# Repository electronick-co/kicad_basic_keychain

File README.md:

# kicad_basic_keychain
a basic keychain made with kicad

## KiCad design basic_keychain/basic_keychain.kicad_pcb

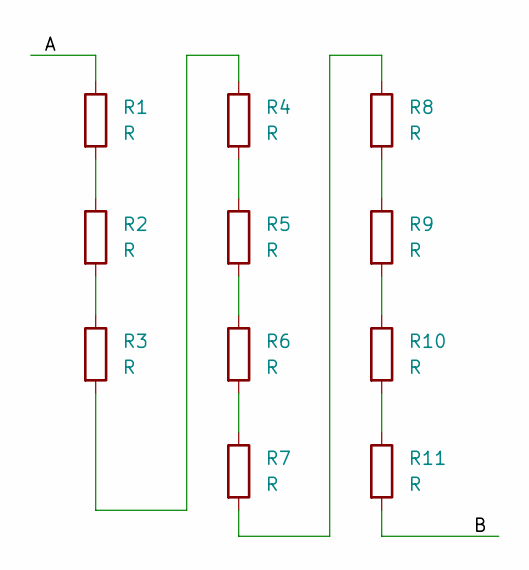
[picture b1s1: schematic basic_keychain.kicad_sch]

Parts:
R1, R2, R3: R; R_1206_3216Metric
R4, R5, R6: R; R_0805_2012Metric
R7, R8, R9: R; R_0603_1608Metric
R10, R11: R; R_0402_1005Metric

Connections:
/A: R1.1
/B: R11.2
unnamed: R1.2, R2.1
unnamed: R2.2, R3.1
unnamed: R3.2, R4.1
unnamed: R4.2, R5.1
unnamed: R5.2, R6.1
unnamed: R6.2, R7.1
unnamed: R7.2, R8.1
unnamed: R8.2, R9.1
unnamed: R9.2, R10.1
unnamed: R10.2, R11.1

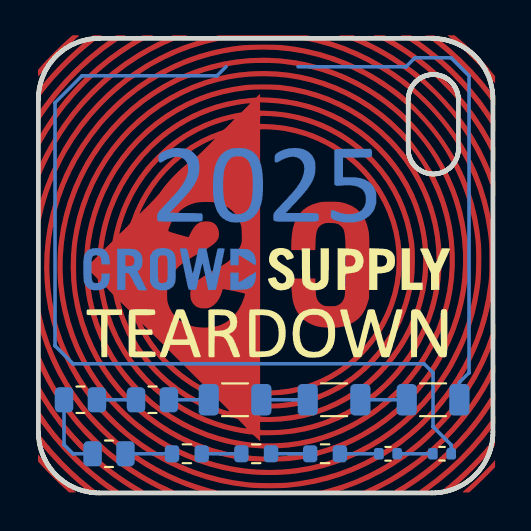
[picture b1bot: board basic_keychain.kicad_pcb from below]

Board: 2 copper layers, 25.3 x 25.3 mm, 11 parts (11 on the bottom side), 10 nets.

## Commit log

2025-06-20 first versions added
